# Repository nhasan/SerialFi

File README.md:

# SerialFi
## Introduction
SerialFi allows you to stream serial data from a micro-controller board to browser clients using any `ESP8266` based board. The firmware is developed and tested on a NodeMCU board but should work on any `ESP8266` based board with little or no modifications. The firmware also allows to send textual data back to the device from the wen interface, allowing two-way communication with the micro-controller board.

## Connection
The figure below shows a NodeMCU board with SerialFi firmware connected to an Arduino Uno. Since the Arduino is a 5v device, a Zener diode (1N4148) is used on the TX pin of the arduino for level shifting as the NodeMCU is only 3.3v tolerant. SerialFi uses the `SoftwareSerial` library on the pins below for serial communication.

| ESP8266 pin | GPIO # | Function |
|-------------|--------|----------|
| D1          | GPIO5  | TX       |
| D2          | GPIO4  | RX       |

## Usage
Upon startup, SerialFi tries to connect to the last used WiFi network. If it is unable to connect or this is the first boot, it creates a network called *SerialFiXXXX* where XXXX is a hex string based on the ESP8266 chip id. When connected to this SSID, it redirects to the WiFi setup page to facilitate the connection to the local WiFi network. Once connected to this local WiFi network, just visit the web app at http://ip.address.of.esp8266/. Here you can select the baud rate that the ESP8266 Software UART would connect with the micro-controller. If all gows well, you should start to see the serial data from the micro-controller in the web app.

The figure below shows the screenshot of the web interface of SerialFi.

## Arduino Shield
The `arduino` folder contains the Kicad design files for the SerialFi Arduino shield. This shield uses a Wemos D1 Mini or compatible ESP8266 dev board. It also has a small prototyping area with +5V, +3.3V and GND traces.

### Schematic

### Rendering

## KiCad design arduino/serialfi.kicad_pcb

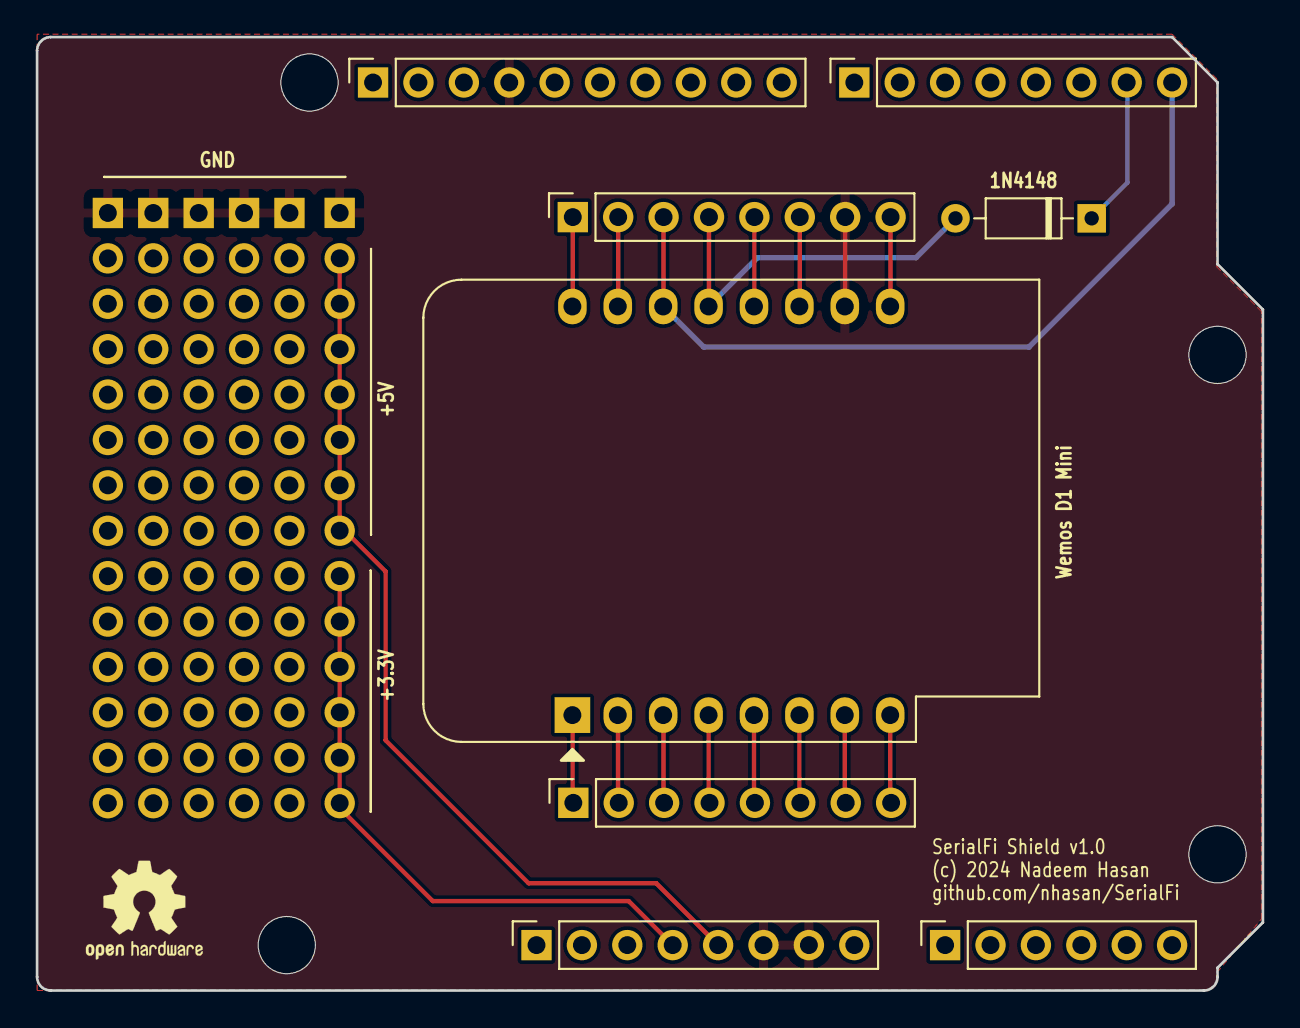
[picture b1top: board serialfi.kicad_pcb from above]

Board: 2 copper layers, 68.6 x 53.3 mm, 18 parts (0 on the bottom side), 21 nets.

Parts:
C1, C2, C3, C4, C5, C6: PinSocket_1x14_P2.54mm_Vertical
D1: 1N4148; D_DO-35_SOD27_P7.62mm_Horizontal
J1: Power; PinSocket_1x08_P2.54mm_Vertical
J2: Digital/PWM; PinSocket_1x10_P2.54mm_Vertical
J3: Analog; PinSocket_1x06_P2.54mm_Vertical
J4, J5, J6: Digital/PWM; PinSocket_1x08_P2.54mm_Vertical
MH1, MH2, MH3, MH4: MountingHole_3.2mm
Wemos D1 Mini: WeMos_D1_mini; WEMOS_D1_mini_light

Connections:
+3V3: C6.9, C6.10, C6.11, C6.12, C6.13, C6.14, J1.4
+5V: C6.2, C6.3, C6.4, C6.5, C6.6, C6.7, C6.8, J1.5
/3V3: J5.8, Wemos D1 Mini.8 (3V3)
/5V: J6.8, Wemos D1 Mini.9 (5V)
/A0': J5.2, Wemos D1 Mini.2 (A0)
/CS/D8: J5.7, Wemos D1 Mini.7 (CS/D8)
/D0': J5.3, Wemos D1 Mini.3 (D0)
/D3: J6.5, Wemos D1 Mini.12 (D3)
/D4: J6.6, Wemos D1 Mini.11 (D4)
/MISO/D6: J5.5, Wemos D1 Mini.5 (MISO/D6)
/MOSI/D7: J5.6, Wemos D1 Mini.6 (MOSI/D7)
/RX: J6.2, Wemos D1 Mini.15 (RX)
/RX/0: J4.8, J6.3, Wemos D1 Mini.14 (SCL/D1)
/SCK/D5: J5.4, Wemos D1 Mini.4 (SCK/D5)
/SCL/A5: J2.1, J3.6
/SDA/A4: J2.2, J3.5
/SRX: D1.2 (A), J6.4, Wemos D1 Mini.13 (SDA/D2)
/TX: J6.1, Wemos D1 Mini.16 (TX)
/TX/1: D1.1 (K), J4.7
/~RST: J5.1, Wemos D1 Mini.1 (~RST)
GND: C1.1, C2.1, C3.1, C4.1, C5.1, C6.1, J1.6, J1.7, J2.4, J6.7, Wemos D1 Mini.10 (GND)

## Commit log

2024-02-13 Initial commit.
2024-02-19 Added Fritzing diagram.
2024-02-19 Added screenshot of the web interface.
2024-02-25 Changes for v0.2
2024-03-23 Arduino shield Kicad PCB and schematic.
2024-03-23 More Arduino Shield stuff.
2024-03-23 More Arduino shield updates.
2024-03-24 Changes for v0.3.
2024-03-24 Added more stuff to ignore.
2024-03-24 Added the zipped production ready gerber files.

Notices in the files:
arduino/serialfi.kicad_pcb:
(c) 2024 Nadeem Hasan
